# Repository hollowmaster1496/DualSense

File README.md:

# DualSense

### Introduction

The objective of this project is to provide an alternative navigation solution for visually-impaired people. The system detects objects using proximity sensors and provides feedback through vibrations so that users can safely navigate in the presence of obstacles. Different feedback schemes are used to distinguish obstacles by proximity. 

Group (2019.047): Haseeb Syed, Ahsan Shahid, Jerry Zhang, Zain Jafri

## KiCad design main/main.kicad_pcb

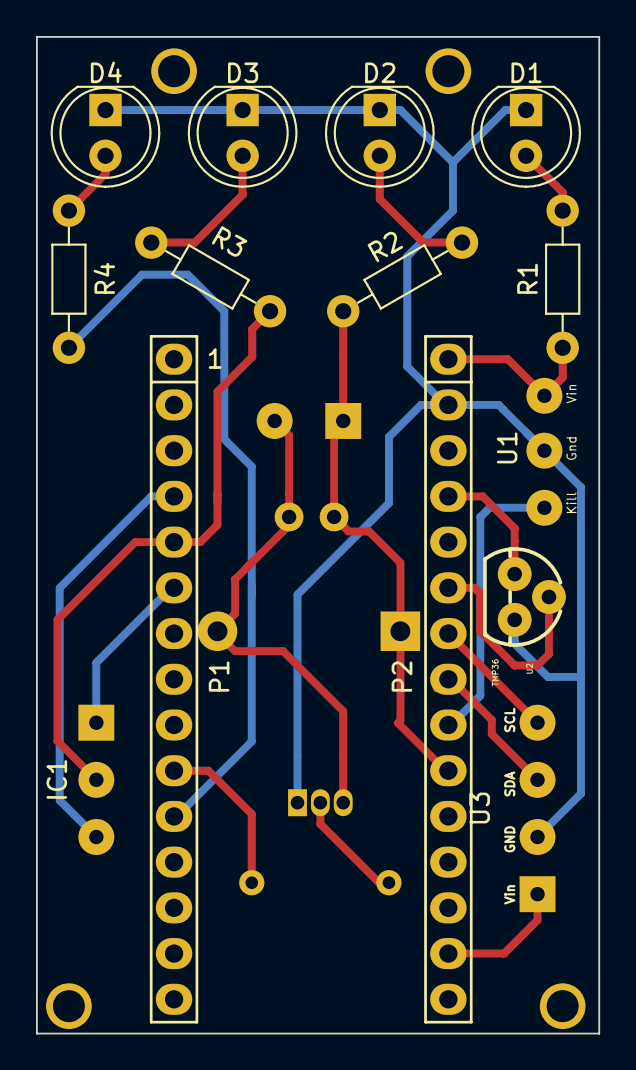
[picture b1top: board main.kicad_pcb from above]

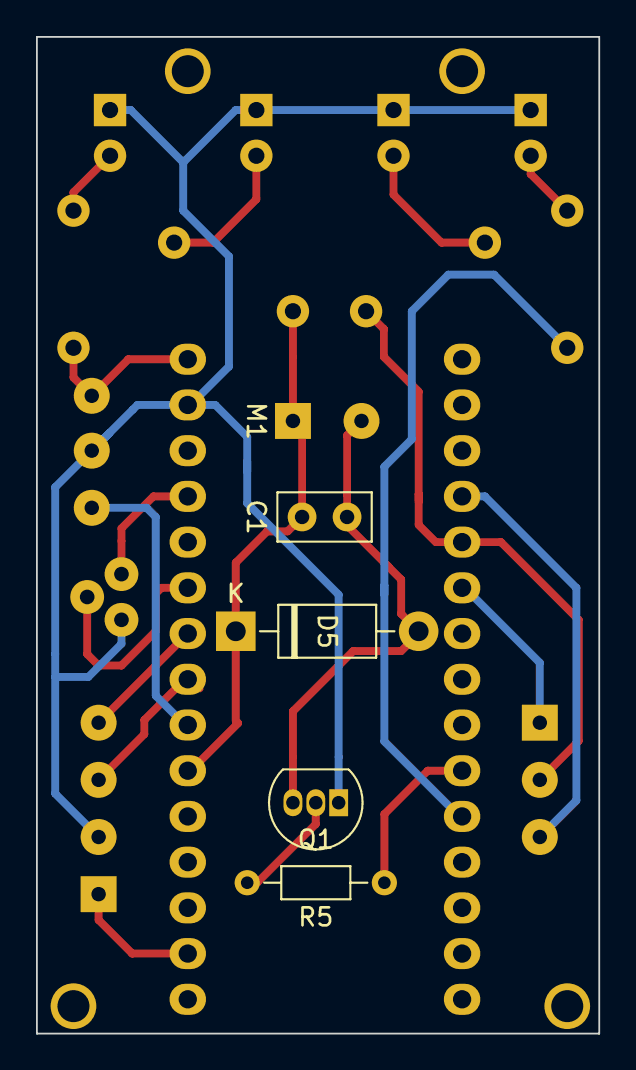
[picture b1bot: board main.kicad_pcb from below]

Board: 2 copper layers, 31.2 x 55.4 mm, 23 parts (5 on the bottom side), 20 nets.

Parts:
C1: 0.1 uF; C_Disc_D5.0mm_W2.5mm_P2.50mm
D1: PWR_GREEN; LED_D5.0mm
D2: MTR_RED; LED_D5.0mm
D3: USONIC_BLUE; LED_D5.0mm
D4: TEMP_YELLOW; LED_D5.0mm
D5: 1N4001; D_DO-41_SOD81_P10.16mm_Horizontal
IC1: MB1010-000; SolderWirePad_1x03_P3.175mm_Drill0.8mm
M1: Motor_DC; SolderWirePad_1x02_P3.81mm_Drill0.8mm
P1: Digital; Socket_Strip_Arduino_1x15
P2: Analog; Socket_Strip_Arduino_1x15
P3, P4, P5, P6: CONN_01X01; 1pin_Nano
Q1: PN2222A; TO-92_Inline
R1, R2, R3, R4, R5: 1K; R_Axial_DIN0204_L3.6mm_D1.6mm_P7.62mm_Horizontal
U1: SW_PWR_BTN; SolderWirePad_3holes_1x03_P3.175mm_Drill0.8mm
U2: TMP36; TO-92
U3: LIS3DH; SolderWirePad_1x04_P3.175mm_Drill0.8mm_LIS3DH_I2C

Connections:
+3V3: P2.14, U3.14
+5V: P2.4, U2.1
/2: IC1.2, P1.5, R3.1
/3(**): IC1.6, P1.6
/7: P1.10, R5.1
/8: P1.11, R4.1
/A2: C1.1, D5.1, M1.1, P2.10, R2.1
/A3: P2.9, U1.4
/A4: P2.8, U3.6
/A5: P2.7, U3.4
/A6: P2.6, U2.2
/Reset: P1.3, P2.3
/Vin: P2.1, R1.1, U1.2
GND: D1.1, D2.1, D3.1, D4.1, IC1.7, P1.4, P2.2, Q1.1, U1.3, U2.3, U3.5
unnamed: C1.2, D5.2, M1.2, Q1.3
unnamed: D1.2, R1.2
unnamed: D2.2, R2.2
unnamed: D3.2, R3.2
unnamed: D4.2, R4.2
unnamed: Q1.2, R5.2

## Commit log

2019-01-13 initial commit: Created new KiCad repository
2019-01-13 main.sch: Added Battery Interface
    This contains a duplicate of the Arduino Nano on-board
    voltage regulator. This is specifically for the positioning
    the heat dissipation system.
2019-01-13 main: Added template for Arduino Nano Shield
2019-01-13 main.sch: Added motor interface with digital control
    The digital signal on pin D7 is used to activate the motor.
    The strength of the motor is controlled by analogue voltage signal
    from pin A7.
2019-01-18 Settings: Added project name and comments
2019-01-18 lib: Added symbols and footprints of three components:
    MB1010 - ultrasonic rangefinder sensor
    GY-521 - ITG/MPU gyroscope+accelerometer
    ARDUINO_NANO - Arduino Nano board
2019-01-18 main.pcb: Enlarged outline of board and translated mounting holes
2019-01-20 main.sch: Added RangeFinder and Accelerometer Interfaces
2019-01-20 main: Added sym lib table
2019-01-21 main.sch: Added Temperature sensor
2019-01-21 lib: Added custom library with adafruit symbols and footprints
2019-01-21 main.sch: Added adafruit push button and re-introduced battery
2019-01-25 main.sch: Added Status Indicator LEDs
    Green: Power ON
    Red: Motor ON
    Blue: Ultrasonic Sensor Active
    Yellow: Temperature HIGH
2019-01-25 main.sch: Replaced capacitor for motor interface with 0.1 uF
2019-01-25 main.sch: Modified wire lengths for compactness
2019-01-26 main.sch: Added missing footprints to symbols
2019-01-26 main.net: Updated netlist with updated footprints
2019-01-26 main.sch: Added footprints for LEDS
2019-01-26 lib: Added libraries for TMP36 and accelerometer
2019-01-26 pcb: Performed preliminary layout without traces
2019-01-26 main.sch: Replaced temperature sensor with through-hole
2019-01-26 pcb: Updated netlist with new TMP36 sensor and re-arranged layout
2019-01-26 pcb: Removed footprints for rangefinder sensor and push button
    These were taking up a lot of room and team decided to connect
    them using wires instead.
2019-01-26 pcb: Performed layout of components to minimize size
    The current layout closely matches size of battery holder footprint.
    This arrangement does not yet have traces added.
2019-01-26 pcb: Fixed mismatching endpoints of board outline
2019-02-04 pcb: Fixed Power button wirepad footprint
2019-02-05 net: Replaced footprint of accelerometer with wire pads
2019-02-05 pcb: Corrected accelerometer I2C wirepad connections
2019-02-05 pcb: Enlarged all trace widths to 0.44mm to allow printing at
    E5 prototyping center
2019-02-05 lib: Updated footprints for new wirepads
2019-02-05 gerbers: Generated Rev 0 Gerber files
2019-02-17 main.pcb: Reassigned pins because A7 is input ONLY
    New pin assignment:
    A6 - Temperature input
    A4 - Motor Output Control
    A5 - Kill Power
2019-02-17 LIS3DH: Updated footprint due to mislabled SDA and SCL
2019-02-17 main.pcb: Reassigned pins to reserve A4 and A5 for accelerometer
2019-02-17 main.pcb: Resolved disconnections and stray traces using Design Rules Check
2019-02-17 main.sch: Replaced 5V line with D3 to control turn ON/OFF ultrasonic sensor
2019-02-17 Gerber: Generated new gerber files with latest revisions applied
2020-10-08 README.md: Initial commit of project description
